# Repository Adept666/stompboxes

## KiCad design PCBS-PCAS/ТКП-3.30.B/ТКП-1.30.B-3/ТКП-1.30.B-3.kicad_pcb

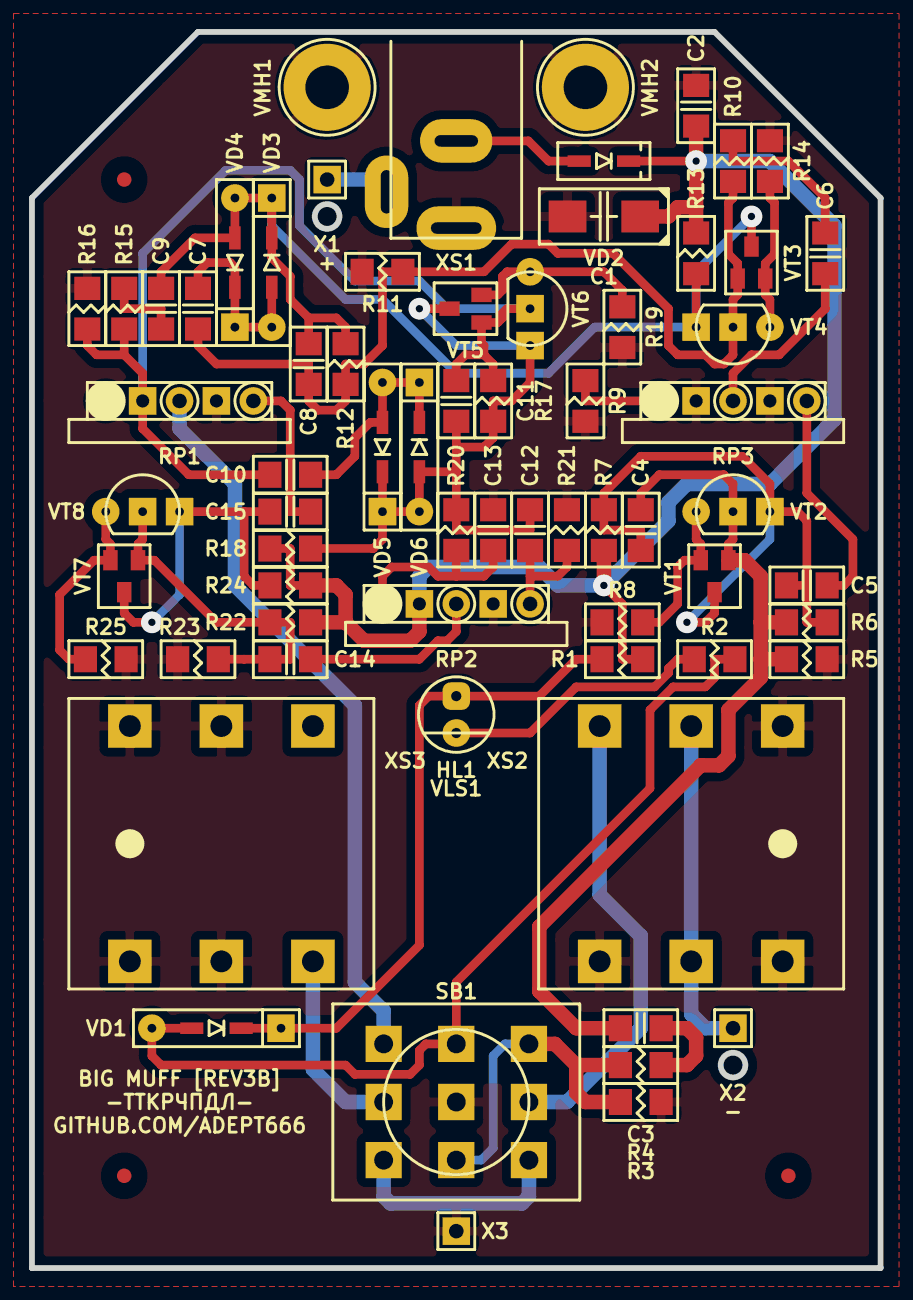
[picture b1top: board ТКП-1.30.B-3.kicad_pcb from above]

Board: 2 copper layers, 58.4 x 85.1 mm, 74 parts (0 on the bottom side), 37 nets.

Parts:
C1: 106; CP-CTSMD-C
C2: 104; C-SM-1206
C3, C5, C6, C7, C9, C10, C14, C15: 105; C-SM-1206
C4, C8, C11: 471; C-SM-1206
C12: 392; C-SM-1206
C13: 103; C-SM-1206
GB1: X; B-PP3-HV
HL1: FYL-5013UWC; LED-ROUND-05.0-UNI-SH-SPACER-PNL-5.3
R1: 0; R-SM-1206
R2, R7, R10, R13, R15, R18, R24: 103; R-SM-1206
R3: 105; R-SM-1206
R4: 393; R-SM-1206
R5, R11, R16, R23: 104; R-SM-1206
R6: 514; R-SM-1206
R8: 101; R-SM-1206
R9: 182; R-SM-1206
R12, R17, R22: 474; R-SM-1206
R14, R19: 391; R-SM-1206
R20, R21: 223; R-SM-1206
R25: 202; R-SM-1206
RP1, RP3: A100K; RPB-18-1x17-1.6-PNL-7.2
RP2: B100K; RPB-18-1x17-1.6-PNL-7.2
SB1: PBS-24-302SP; SW-PBS-24-302SP-2.5-PNL-12.0
VD1: X; P-SOD-123-OR-DO-35-V2
VD2: 0520; P-SOD-123
VD3, VD4, VD5, VD6: 6263; P-SOD-123-OR-DO-35-V2
VE1: ТКП-6.3.1.A2.A1.A.1-1; ТКП-6.3.1.A2.A1.A
VE2: ТКП-6.3.3.A1.A1.3-1.A1.00; ТКП-6.3.3.A1
VFM1, VFM2, VFM3: 1.0; VFM-1.0-3.0-SL
VLS1: BR-17.8; VLS-BR-P
VMH1, VMH2: DI5M3x20; VMH-STA-DA5-PNL-3.0
VT1, VT3, VT5, VT7: 5088; P-SOT-23-B-E-C
VT2, VT4, VT6, VT8: 5088; P-TO-92-E-B-C
X1, X2, X3: X; CON-PAD-S-1.0-1.9
XS1: DC-005; CON-DC-005-9V-OVAL
XS2, XS3: PJ-644C; CON-PJ-644C-IN-OR-OUT

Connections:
/1B: C3.2, C4.1, R5.2, R6.1, VT1.B, VT2.B
/1C: C4.2, C5.1, R6.2, R7.1, VT1.C, VT2.C
/1E: R8.2, VT1.E, VT2.E
/2B: C7.1, C8.1, R10.2, R11.2, R12.1, VT3.B, VT4.B
/2C: C8.2, C9.1, R12.2, R13.1, VD3.C, VD4.A, VT3.C, VT4.C
/2E: R14.2, VT3.E, VT4.E
/3B: C10.1, C11.1, R15.2, R16.2, R17.1, RP1.NC1, VT5.B, VT6.B
/3C: C11.2, C12.1, R17.2, R18.1, R20.1, VD5.C, VD6.A, VT5.C, VT6.C
/3E: R19.2, VT5.E, VT6.E
/4B: C14.2, R22.1, R23.2, VT7.B, VT8.B
/4C: C15.1, R24.1, VT7.C, VT8.C
/4E: R25.2, VT7.E, VT8.E
/IN-CIR: R3.2, R4.1, SB1.NC2, SB1.NO3
/IN-CON: SB1.COM3, XS2.T
/LED: R2.1, SB1.NO2, VD1.A
/OUT-CIR: RP1.2, SB1.NO1
/OUT-CON: SB1.COM1, XS3.T
/PP3-NEG: X2.1, XS2.R, XS2.RN
/PP3-POS: X1.1, XS1.SN
COM: C1.-, C2.2, C13.2, R3.1, R5.1, R8.1, R9.1, R11.1, R14.1, R16.1, R19.1, R21.2, R23.1, R25.1, RP1.1, RP1.NC2, RP2.NC2, RP3.NC1, RP3.NC2, SB1.COM2, VMH1.0, VMH2.0, X3.1, XS1.C, XS2.S, XS2.SN, XS2.TN, XS3.R, XS3.RN, XS3.S, XS3.SN
unnamed: C3.1, R4.2
unnamed: C5.2, RP3.3
unnamed: C6.1, RP3.2
unnamed: C6.2, R10.1
unnamed: C7.2, VD3.A, VD4.C
unnamed: C9.2, R15.1
unnamed: C10.2, VD5.A, VD6.C
unnamed: C12.2, R21.1, RP2.3
unnamed: C13.1, R20.2, RP2.1
unnamed: C14.1, RP2.2
unnamed: C15.2, RP1.3
unnamed: HL1.A, R1.2, VD1.C
unnamed: HL1.C, R2.2
unnamed: R9.2, RP3.1
unnamed: SB1.NC1, SB1.NC3
unnamed: VD2.A, XS1.S
V: C1.+, C2.1, R1.1, R7.2, R13.2, R18.2, R22.2, R24.2, RP2.NC1, VD2.C

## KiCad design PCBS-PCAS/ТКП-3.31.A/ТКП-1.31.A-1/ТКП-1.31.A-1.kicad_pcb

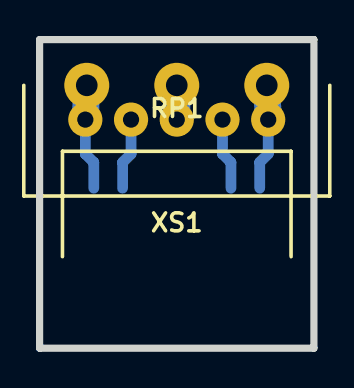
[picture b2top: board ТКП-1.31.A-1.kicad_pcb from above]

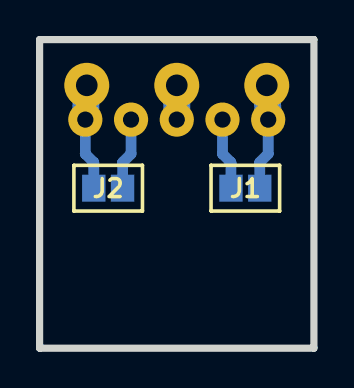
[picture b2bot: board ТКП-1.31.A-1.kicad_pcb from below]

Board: 2 copper layers, 15.2 x 17.1 mm, 4 parts (2 on the bottom side), 5 nets.

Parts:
J1: J1; J-SB-0805-2
J2: J2; J-SB-0805-2
RP1: A100K; RP-PDB181-K-20-P-CIRCULAR
XS1: PBS-05R; CON-PBS-05R-CIRCULAR

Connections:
unnamed: J1.1, RP1.3, XS1.1
unnamed: J1.2, XS1.2
unnamed: J2.1, XS1.4
unnamed: J2.2, RP1.1, XS1.5
unnamed: RP1.2, XS1.3

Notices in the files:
PCBS-PCAS/ТКП-3.30.B/ТКП-1.30.B-3/ТКП-1.30.B-3.kicad_pcb:
This project is licensed under GNU General Public License v3.0 or later
